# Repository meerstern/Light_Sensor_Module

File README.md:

# Light_Sensor_Module

Light Sensor Module with APDS-9008-020

## 概要 
  * アナログ光センサ[APDS-9008-020][1]を用いた光センサ基板です  
  * 人の目に近いスペクトル応答性と広い照明範囲にわたる出力線形性のセンサを使用しています  
  * 光強度のアナログ出力(A)と可変抵抗で調整可能な閾値によるデジタル出力(D)を備えています  
  * デジタル出力の状態はLEDで確認できます  
  * コネクタはGrove互換コネクタとなっており、3.3V/5V電源に対応しています  
  * 電源は3V~5.5Vに対応しています  
  * 光センサ感度の可変抵抗、デジタル出力の閾値の可変抵抗を備えています  
  * 本センサは環境負荷の大きなCdSを使用していません  
  * 基板サイズ25mm x30mm、固定穴M3x4 幅19mm x24mm  

## 注意 
  * 可変抵抗は強く回したり、速く動かすと破損する場合があります。ゆっくり動かしてください     
  * 基板裏側の光センサは衝撃や外力に非常に弱いため、取り扱いに注意してください    

## 販売サイト
  * [スイッチサイエンス][2]
 
[1]: https://jp.broadcom.com/products/optical-sensors/ambient-light-photo-sensors/apds-9008 "*1"
[2]: https://www.switch-science.com/products/7394
MIT Lisense

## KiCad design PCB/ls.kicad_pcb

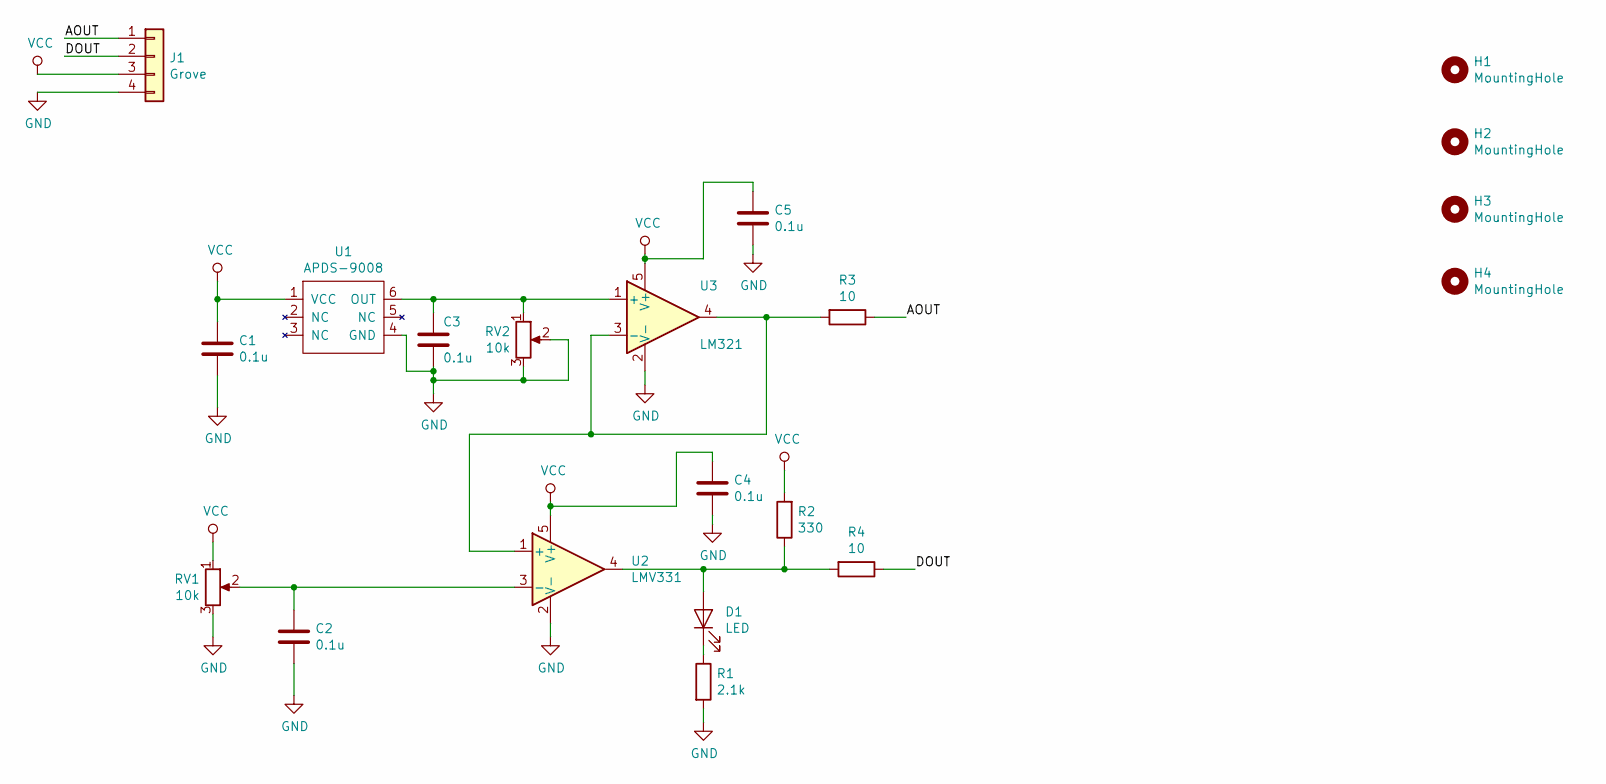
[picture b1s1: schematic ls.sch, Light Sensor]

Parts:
C1, C2, C3, C4, C5: 0.1u; C_0603_1608Metric
D1: LED; LED_0603_1608Metric
H1, H2, H3, H4: MountingHole; MountingHole_3.2mm_M3
J1: Grove; GROVE
R1: 2.1k; R_0603_1608Metric
R2: 330; R_0603_1608Metric
R3, R4: 10; R_0603_1608Metric
RV1, RV2: 10k; rcl-RTRIMCVR42A
U1: APDS-9008
U2: LMV331; SOT-353_SC-70-5
U3: LM321; SOT-353_SC-70-5

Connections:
/AOUT: J1.1, R3.1
/DOUT: J1.2, R4.1
GND: C1.2, C2.2, C3.2, C4.2, C5.2, J1.4, R1.2, RV1.3, RV2.2, RV2.3, U1.4 (GND), U2.2 (V-), U3.2 (V-)
unnamed: C2.1, RV1.2, U2.3 (-)
unnamed: C3.1, RV2.1, U1.6 (OUT), U3.1 (+)
unnamed: D1.1 (K), R1.1
unnamed: D1.2 (A), R2.1, R4.2, U2.4
unnamed: R3.2, U2.1 (+), U3.3 (-), U3.4
VCC: C1.1, C4.1, C5.1, J1.3, R2.2, RV1.1, U1.1 (VCC), U2.5 (V+), U3.5 (V+)

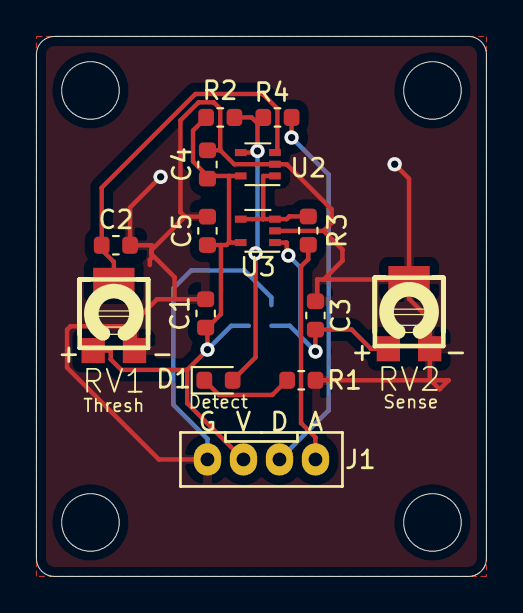
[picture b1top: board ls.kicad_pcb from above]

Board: 2 copper layers, 25.0 x 30.0 mm, 20 parts (1 on the bottom side), 9 nets.

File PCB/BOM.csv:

Elecrow PN,Parts,Value,Package,QTY,Digikey/Mouser/Manufacturer Part,Remark/ Link
,U3,LM321,SOT-353_SC-70-5,1,595-TLV316IDCKR ,
,U2,LMV331,SOT-353_SC-70-5,1,595-LMV331IDCKR,
,U1,APDS-9008,APDS-9008,1,630-APDS-9008-020 ,
,"RV2,RV1",10k,rcl-RTRIMCVR42A,2,652-TC33X-2-103E ,
C22859,"R4,R3",10,R_0603_1608Metric,2,,
C23138,R2,330,R_0603_1608Metric,1,,
C4190,R1,2.2k,R_0603_1608Metric,1,,
,J1,Grove,GROVE,1,713-110990037,
4040806A,D1,LED,LED_0603_1608Metric,1,,
C14663,"C5,C4,C3,C2,C1",0.1u,C_0603_1608Metric,5,,

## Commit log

2021-06-30 Add PCB Files
2021-07-10 Add README
2021-07-31 Add images
2022-12-06 Add shop link
